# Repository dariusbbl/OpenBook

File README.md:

# OpenBook

# Block Diagram

# Hardware Components
#### Microcontroller – ESP32-C6
- **Core Architecture:** 32-bit RISC-V processor  
- **Wireless Support:** Integrated Wi-Fi 6 and Bluetooth Low Energy 5.0  
- **I/O Capabilities:** Supports multiple digital interfaces – SPI, I²C, UART, PWM, and general-purpose IO  
- **Power Features:** Low-energy design with deep sleep functionality for battery-powered applications

#### Real-Time Clock – DS3231SN
- **Accuracy:** ±2 ppm  
- **Communication:** I²C (`SDA`, `SCL`)  
- **Backup Power:** Supercapacitor-based retention

#### E-Paper Display
- **Connection Method:** 20-pin dedicated header  
- **Communication Protocol:** SPI + GPIO  
- **Key Signals:** `EPD_CS`, `EPD_DC`, `EPD_RST`, `EPD_BUSY`, etc.  
- **Advantages:** Zero power draw when idle, high readability in sunlight

#### MicroSD Card Slot
- **Interface:** SPI (connected to IO4 through IO9)  
- **Purpose:** Storing eBooks, setting and user configuration data  

#### Environmental Sensor – BME688
- **Measurements:** Temperature, Humidity, Pressure and VOCs  
- **Interface:** I²C  
- **Pins:** `SDA` – IO1, `SCL` – IO2  
- **Power Supply:** 3.3V  
- **Default Address:** `0x76` 

#### Environmental Sensor – BME688 Battery Fuel Gauge - MAX17048
- **Role:** Estimates remaining charge in LiPo(Lithium Polymer) battery
- **Protocol:** I²C (shared on IO1, IO2)  

#### Environmental Sensor – BME688 I²C Expansion – Qwiic / Stemma QT
- **Connector:** 4-pin (3V3, GND, SDA, SCL)  
- **Protocol:** I²C (`IO1`, `IO2`)  
- **Compatibility:** Plug-and-play with Adafruit / SparkFun modules  

#### Environmental Sensor – BME688 Voltage Supervisor – BD52xx
- **Purpose:** Monitors voltage levels, triggers safe reset  
- **Control Pin:** IO0

#### MCP73831 – Charging Controller
- **Function:** LiPo charging via USB (3.7V)  
- **Charging Current:** ~500 mA  
- **Indicator:** Status LED  

# BOM (Bill Of Materials)

| Componenta | Link | Datasheet |
|-----------|--------------|-----------|
| BUTTON | [Model](https://industry.panasonic.com/global/en/products/control/switch/light-touch/number/evqpuj02k) | [Datasheet](https://www.lcsc.com/datasheet/lcsc_datasheet_2201121800_PANASONIC-EVQPUJ02K_C2936858.pdf) |
| CAPACITOR | [Model](https://componentsearchengine.com/part-view/R0402%201%25%20100%20K%20(RC0402FR-07100KL)/YAGEO) | [Datasheet](//efaidnbmnnnibpcajpcglclefindmkaj/https://www.resistor.com/assets/pdf/0402tstd.pdf) |
| CPH3225A | [Model](https://www.snapeda.com/parts/CPH3225A/Seiko+Instruments/view-part/?ref=eda) | [Datasheet](https://octopart.com/datasheet/cph3225a-seiko-25340571) |
| EVQPUJ02K | [Model](https://industry.panasonic.com/global/en/products/control/switch/light-touch/number/evqpuj02k) | [Datasheet](https://www.lcsc.com/datasheet/lcsc_datasheet_2201121800_PANASONIC-EVQPUJ02K_C2936858.pdf) |
| KP-1608SURCK | [Model](https://www.snapeda.com/parts/KP-1608SURCK/Kingbright/view-part/?ref=search&t=LED%200603) | [Datasheet](//efaidnbmnnnibpcajpcglclefindmkaj/https://media.elv.com/file/107153_led_surck1608_data.pdf) |
| USBLC6-2SC6Y | [Model](https://www.snapeda.com/parts/USBLC6-2SC6Y/STMicroelectronics/view-part/?ref=eda) | [Datasheet](https://www.digikey.com/en/htmldatasheets/production/1375342/0/0/1/usblc6-2sc6y) |
| SD0805S020S1R0 | [Model](https://ro.mouser.com/ProductDetail/KYOCERA-AVX/SD0805S020S1R0?qs=jCA%252BPfw4LHbpkAoSnwrdjw%3D%3D) | [Datasheet](https://www.alldatasheet.com/view.jsp?Searchword=SD0805S&sField=2) |
| PGB1010603MR | [Model](https://www.snapeda.com/parts/PGB1010603MR/Littelfuse/view-part/?ref=eda) | [Datasheet](https://www.alldatasheet.com/view.jsp?Searchword=Pgb1010603mr&gad_source=1&gbraid=0AAAAADcdDU8aYfZtfJfdZ9I5j6RwZ_cbA&gclid=Cj0KCQjwqcO_BhDaARIsACz62vOPBOBe0eOh5gDUFkkKl4JBcbmoFZYtJ8BOnbaWqr_BuUCcVWvbutAaAmGkEALw_wcB) |
| BD5229G-TR  | [Model](https://componentsearchengine.com/part-view/BD5229G-TR/ROHM%20Semiconductor) | [Datasheet](https://www.lcsc.com/datasheet/lcsc_datasheet_2201131330_ROHM-Semicon-BD5229G-TR_C962636.pdf) |
| XC6220A331MR-G | [Model](https://componentsearchengine.com/part-view/XC6220A331MR-G/Torex) | [Datasheet](https://www.alldatasheet.com/view.jsp?Searchword=Xc6220&gad_source=1&gbraid=0AAAAADcdDU8aYfZtfJfdZ9I5j6RwZ_cbA&gclid=Cj0KCQjwqcO_BhDaARIsACz62vPS06NB6tLgniZzfaVpKNu1m811BNk6AEPfg4DbP6f5S8QWA_pW_UQaAv-0EALw_wcB) |
| XC6220A331MR-G | [Model](https://componentsearchengine.com/part-view/XC6220A331MR-G/Torex) | [Datasheet](https://www.alldatasheet.com/view.jsp?Searchword=Xc6220&gad_source=1&gbraid=0AAAAADcdDU8aYfZtfJfdZ9I5j6RwZ_cbA&gclid=Cj0KCQjwqcO_BhDaARIsACz62vMO5_aHsn35cIZBK6oCFuB_WOxz_zKu4yOHJ69-EnaUd5Jfas_Avm8aAuk5EALw_wcB) |
| USB4110-GF-A  | [Model](https://componentsearchengine.com/part-view/USB4110-GF-A/GCT%20(GLOBAL%20CONNECTOR%20TECHNOLOGY)) | [Datasheet](//efaidnbmnnnibpcajpcglclefindmkaj/https://gct.co/files/drawings/usb4110.pdf) |
| Adafruit | [Model](https://eu.mouser.com/ProductDetail/Adafruit/4208?qs=PzGy0jfpSMtbScLbr0L5dw%3D%3D) | [Datasheet](https://www.arrow.com/en/manufacturers/adafruit-industries/datasheets) |
| Bobina | [Model](https://store.comet.srl.ro/Catalogue/Product/43497/) | [Datasheet](https://www.scribd.com/document/814581278/Datasheet-Bobina) |
| PFMF | [Model](https://www.mouser.co.uk/ProductDetail/EPCOS-TDK/B72520T0350K062?qs=dEfas%2FXlABIszF52uu7vrg%3D%3D) | [Datasheet](https://ro.mouser.com/c/ds/circuit-protection/thermistors/resettable-fuses-pptc/?m=Schurter&series=PFMF) |
| DMG2305UX-7 | [Model](https://componentsearchengine.com/part-view/DMG2305UX-7/Diodes%20Incorporated) | [Datasheet](//efaidnbmnnnibpcajpcglclefindmkaj/https://www.mouser.com/datasheet/2/115/DMG2305UX-266242.pdf?srsltid=AfmBOop22k34YTJJra1xubiU6LPiN4M4JlcWbRoSNdxSGFak8uWgXPpK) |
| Si1308EDL-T1-GE3 | [Model](https://componentsearchengine.com/part-view/SI1308EDL-T1-GE3/Vishay) | [Datasheet](https://www.alldatasheet.com/view.jsp?Searchword=Si1308edl&gad_source=1&gbraid=0AAAAADcdDU-px713ONYSnQ2O-gcwqYcFq&gclid=Cj0KCQjwqcO_BhDaARIsACz62vN_Nz3MJOc6J_03gnVBm7aSqC8v9wyP0VD-iRKP-gFrYgdhLi99I14aAlVJEALw_wcB) |
| R0402 | [Model](https://componentsearchengine.com/part-view/R0402%201%25%20100%20K%20(RC0402FR-07100KL)/YAGEO) | [Datasheet](//efaidnbmnnnibpcajpcglclefindmkaj/https://www.resistor.com/assets/pdf/0402tstd.pdf) |
| BME680 | [Model](https://www.snapeda.com/parts/BME680/Bosch/view-part/?welcome=home) | [Datasheet](//efaidnbmnnnibpcajpcglclefindmkaj/https://www.bosch-sensortec.com/media/boschsensortec/downloads/datasheets/bst-bme680-ds001.pdf) |
| SMD Solder | [Model](https://grabcad.com/library/solder-jumpers-1) | [Datasheet]() |
| W25Q512JVEIQ | [Model](https://www.snapeda.com/parts/ESP32-C6-WROOM-1-N8/Espressif+Systems/view-part/?ref=eda) | [Datasheet](//efaidnbmnnnibpcajpcglclefindmkaj/https://www.mouser.com/datasheet/2/949/W25Q512JV_SPI_RevB_06252019_KMS-2487502.pdf?srsltid=AfmBOoquExqDVgxEELF9CzuOGxHos0CD1nQDROHD6Eebdm2foNzqozqU) |
| ESP32-C6-WROOM-1-N8 | [Model](https://www.snapeda.com/parts/ESP32-C6-WROOM-1-N8/Espressif+Systems/view-part/?ref=eda) | [Datasheet](//efaidnbmnnnibpcajpcglclefindmkaj/https://www.mouser.com/catalog/specsheets/Espressif_ESP32_C6_WROOM_1%20_Datasheet_V0.1_PRELIMINARY_en.pdf?srsltid=AfmBOooHQKNitqODRaaPjoZInfWKTacDER1t5uRK6sKqT13TrzvVo_B7) |
| DS3231SN# | [Model](https://www.snapeda.com/parts/DS3231SN%23/Analog+Devices/view-part/?ref=eda) | [Datasheet](https://www.alldatasheet.com/view.jsp?Searchword=Ds3231sn%20datasheet&gad_source=1&gbraid=0AAAAADcdDU-Gy9URfMxGmqiPg7ci5L3wR&gclid=Cj0KCQjwqcO_BhDaARIsACz62vMkK3ETSnW2w7mo0Fa-wgWJGn89AxWCyIND6k5X8MmoPl6hv6VWwT8aAiS-EALw_wcB) |
| MAX17048G+T10 | [Model](https://www.snapeda.com/parts/MAX17048G+T10/Analog+Devices/view-part/?ref=eda) | [Datasheet](https://www.alldatasheet.com/view.jsp?Searchword=Max17048&gad_source=1&gbraid=0AAAAADcdDU8aYfZtfJfdZ9I5j6RwZ_cbA&gclid=Cj0KCQjwqcO_BhDaARIsACz62vNa9xrVfzjCjADRwXD0RBbo4Nret3ywwteDGLJKZui8ZL8KdVlTE7caAvQxEALw_wcB) |
| MCP73831T-5ACI/OT | [Model](https://www.mouser.co.uk/ProductDetail/Microchip-Technology/MCP73831T-5ACI-OT?qs=hH%252BOa0VZEiAcgAcEkuamXg%3D%3D) | [Datasheet](//efaidnbmnnnibpcajpcglclefindmkaj/https://ww1.microchip.com/downloads/en/DeviceDoc/MCP73831-Family-Data-Sheet-DS20001984H.pdf) |

### ESP32-C6 Hardware Connections Overview  

| **Peripheral**               | **Connected Pin(s)**                                             | **Protocol** | **Functionality Description** |
|-----------------------------|------------------------------------------------------------------|--------------|-------------------------------|
| **E-Paper Display**         | IO7 (MOSI), IO6 (SCK), IO10 (CS), IO5 (DC), IO23 (RST), IO3 (BUSY) | SPI          | Sends visual data and manages display operations. |
| **MicroSD Card Module**     | IO7 (MOSI), IO6 (SCK), IO4 (SS_SD), IO2 (MISO)                   | SPI          | Enables saving and reading of e-book files. |
| **BME688 Environmental Sensor** | IO21 (SDA), IO22 (SCL)                                        | I2C          | Measures environmental factors like temperature, humidity, pressure, and gas levels. |
| **DS3231 RTC Module**       | IO21 (SDA), IO22 (SCL), IO18 (RST), IO1 (32KHz), IO0 (INT_RTC)   | I2C          | Maintains accurate timekeeping even when the main system is off. |
| **External NOR Flash**      | IO11 (CS), IO6 (SCK), IO2 (MISO), IO7 (MOSI)                     | SPI          | Offers extra non-volatile memory for storing application-specific data. |
| **Battery Status Monitor**  | IO21 (SDA), IO22 (SCL)                                           | I2C          | Monitors power level and battery condition. |
| **USB-C Interface**         | GPIOs via regulated voltage lines                                | USB          | Supplies power and facilitates programming access. |
| **User Input Buttons**      | IO9 (BOOT), IO15 (CHANGE), EN (RESET)                            | GPIO         | Detects user interaction through physical button presses. |

# Decision & Modifications
- To address the design checker errors, I adjusted the dimensions of several components.
- The main components were positioned exactly according to the provided specifications to ensure a perfect match between the PCB dimensions and the case. Component placement was carefully planned to allow for efficient routing. The battery was placed in the remaining free space within the case.
- A ground plane was created on both the top and bottom layers to improve signal integrity and reduce noise.
- Routing was performed on both the top and bottom layers. Power traces were placed exclusively on the top layer to avoid the use of vias.
- Diodes (SMD-Hole): The initial footprint included through-hole pads that were too narrow, potentially leading to soldering difficulties and poor connectivity. To address this, the pad dimensions were modified to 35 mil × 190 mil, improving both manufacturability and the reliability of the electrical contact.
- U4 – MAX17048G+T10: The VBAT power trace was routed with a width of 0.3 mm due to design constraints. However, the original footprint featured pin widths of just 0.27 mm, which caused mismatches and disrupted routing symmetry. The pad widths were therefore increased to match the trace width, ensuring consistent routing and improved layout balance.

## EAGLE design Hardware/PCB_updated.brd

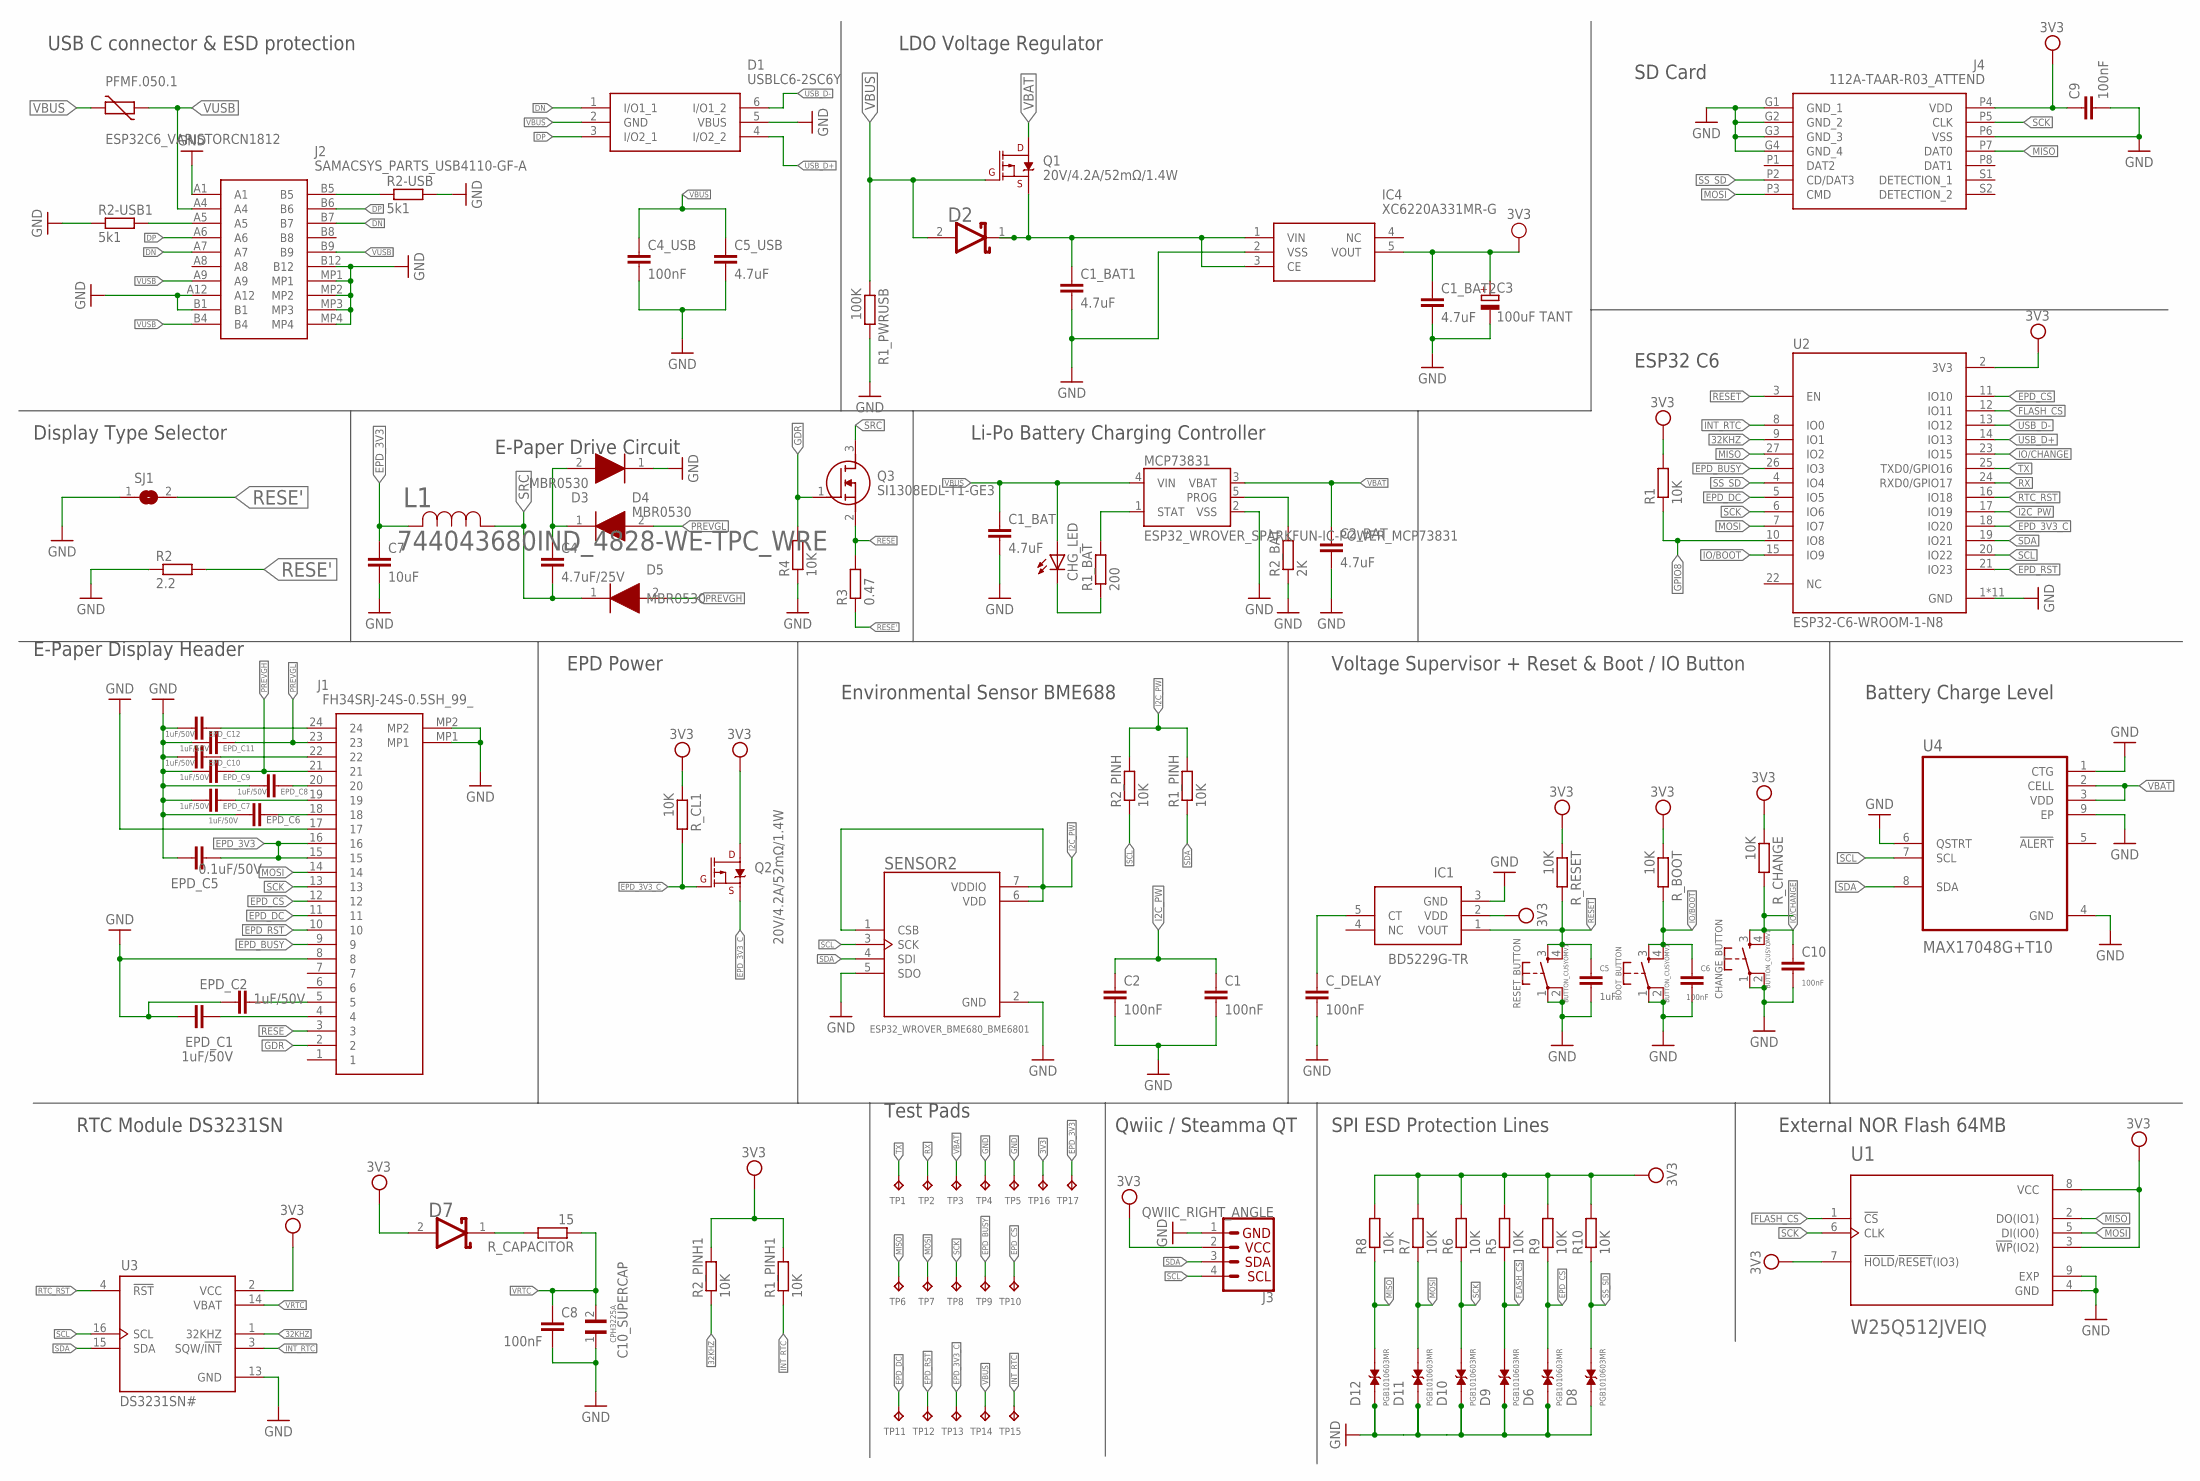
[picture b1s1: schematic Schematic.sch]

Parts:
BOOT_BUTTON: BUTTON_CUSYOMV1; MYBUTTON
C1, C2, C4_USB, C6, C8, C9, C10: 100nF; ESP32_WROVER_EAGLE-LTSPICE_C0402
C1_BAT, C1_BAT1, C1_BAT2, C2_BAT, C5_USB: 4.7uF; ESP32_WROVER_EAGLE-LTSPICE_C0402
C3: 100uF TANT; RCL_CT3528
C4: 4.7uF/25V; ESP32_WROVER_EAGLE-LTSPICE_C0402
C5: 1uF; ESP32_WROVER_EAGLE-LTSPICE_C0402
C7: 10uF; ESP32_WROVER_EAGLE-LTSPICE_C0402
C10_SUPERCAP: CPH3225A; CAPCP3225X100N
CHANGE_BUTTON: BUTTON_CUSYOMV1; MYBUTTON
CHG_LED: ADAFRUIT_LEDCHIP-LED0603; ADAFRUIT_CHIP-LED0603
C_DELAY: 100nF; ESP32_WROVER_EAGLE-LTSPICE_C0402
D1: USBLC6-2SC6Y; SOT95P280X145-6N
D2, D7: ESP32_WROVER_AVX---SD0805S020S1R0_AVX_SD0805S020S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; ESP32_WROVER_AVX---SD0805S020S1R0_AVX_SD0805S020S1R0_0
D3, D4, D5: MBR0530; SOD3716X135N
D6, D8, D9, D10, D11, D12: PGB1010603MR; DIOC1608X36N
EPD_C1, EPD_C2, EPD_C6, EPD_C7, EPD_C8, EPD_C9, EPD_C10, EPD_C11, EPD_C12: 1uF/50V; ESP32_WROVER_EAGLE-LTSPICE_C0402
EPD_C5: 0.1uF/50V; ESP32_WROVER_EAGLE-LTSPICE_C0402
IC1: BD5229G-TR; SOT95P280X125-5N
IC4: XC6220A331MR-G; SOT95P280X120-5N
J1: FH34SRJ-24S-0.5SH_99_; FH34SRJ24S05SH99
J2: SAMACSYS_PARTS_USB4110-GF-A; SAMACSYS_PARTS_USB4110GFA
J3: QWIIC_RIGHT_ANGLE; JST04_1MM_RA
J4: 112A-TAAR-R03_ATTEND; 112ATAARR03ATTEND
L1: 744043680IND_4828-WE-TPC_WRE; IND_4828-WE-TPC_WRE
MCP73831: ESP32_WROVER_SPARKFUN-IC-POWER_MCP73831; ESP32_WROVER_SPARKFUN-IC-POWER_SOT23-5
PFMF.050.1: ESP32C6_VARISTORCN1812; ESP32C6_VARISTOR_CT/CN1812
Q1, Q2: 20V/4.2A/52mΩ/1.4W; ESP32_WROVER_SPARKFUN-DISCRETESEMI_SOT23-3
Q3: SI1308EDL-T1-GE3; SOT65P210X110-3N
R1, R1_PINH, R1_PINH1, R2_PINH, R2_PINH1, R4, R5, R6, R7, R9, R10: 10K; ESP32_WROVER_EAGLE-LTSPICE_R0402
R1_BAT: 200; ESP32_WROVER_EAGLE-LTSPICE_R0402
R1_PWRUSB: 100K; ESP32_WROVER_EAGLE-LTSPICE_R0402
R2: 2.2; ESP32_WROVER_EAGLE-LTSPICE_R0402
R2-USB, R2-USB1: 5k1; ESP32_WROVER_EAGLE-LTSPICE_R0402
R2_BAT: 2K; ESP32_WROVER_EAGLE-LTSPICE_R0402
R3: 0.47; ESP32_WROVER_EAGLE-LTSPICE_R0402
R8: 10k; ESP32_WROVER_EAGLE-LTSPICE_R0402
RESET_BUTTON: BUTTON_CUSYOMV1; MYBUTTON
R_BOOT: 10K; ESP32_WROVER_EAGLE-LTSPICE_R0402
R_CAPACITOR: 15; ESP32_WROVER_EAGLE-LTSPICE_R0402
R_CHANGE: 10K; ESP32_WROVER_EAGLE-LTSPICE_R0402
R_CL1: 10K; ESP32_WROVER_EAGLE-LTSPICE_R0402
R_RESET: 10K; ESP32_WROVER_EAGLE-LTSPICE_R0402
SENSOR2: ESP32_WROVER_BME680_BME6801; ESP32_WROVER_BME680_PSON80P300X300X100-8N
SJ1: SJ
TP1, TP2, TP3, TP4, TP5, TP6, TP7, TP8, TP9, TP10, TP11, TP12, TP13, TP14, TP15, TP16, TP17: TPTP20R; TP20R
U1: W25Q512JVEIQ; SON127P600X800X80-9N
U2: ESP32-C6-WROOM-1-N8; XCVR_ESP32-C6-WROOM-1-N8
U3: DS3231SN#; SOIC127P1032X265-16N
U4: MAX17048G+T10; SON50P200X200X80-9N

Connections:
3V3: C1_BAT2.1, C3.+, C9.1, D7.2 (ANODE), IC1.2 (VDD), IC4.5 (VOUT), J3.2, J4.P4 (VDD), Q2.3 (D), R1.2, R1_PINH1.2, R2_PINH1.2, R5.2, R6.2, R7.2, R8.2, R9.2, R10.2, R_BOOT.1, R_CHANGE.1, R_CL1.1, R_RESET.1, TP16.TP, U1.3 (!WP!(IO2)), U1.7 (!HOLD!/!RESET!(IO3)), U1.8 (VCC), U2.2 (3V3), U3.2 (VCC)
32KHZ: R2_PINH1.1, U2.9 (IO1), U3.1 (32KHZ)
DN: D1.1 (I/O1_1), J2.A7, J2.B7
DP: D1.3 (I/O2_1), J2.A6, J2.B6
EPD_3V3: C7.1, EPD_C5.2, J1.15, J1.16, L1.2, TP17.TP
EPD_3V3_C: Q2.1 (G), Q2.2 (S), R_CL1.2, TP13.TP, U2.18 (IO20)
EPD_BUSY: J1.9, TP9.TP, U2.26 (IO3)
EPD_CS: D6.2, J1.12, R9.1, TP10.TP, U2.11 (IO10)
EPD_DC: J1.11, TP11.TP, U2.5 (IO5)
EPD_RST: J1.10, TP12.TP, U2.21 (IO23)
FLASH_CS: D9.2, R5.1, U1.1 (!CS), U2.12 (IO11)
GDR: J1.2, Q3.1 (G), R4.2
GND: BOOT_BUTTON.1, BOOT_BUTTON.2, C1.2, C1_BAT.2, C1_BAT1.2, C1_BAT2.2, C2.2, C2_BAT.2, C3.-, C4_USB.2, C5.2, C5_USB.2, C6.2, C7.2, C8.2, C9.2, C10.2, C10_SUPERCAP.1, CHANGE_BUTTON.1, CHANGE_BUTTON.2, C_DELAY.2, D1.5 (VBUS), D3.1 (K), D6.1, D8.1, D9.1, D10.1, D11.1, D12.1, EPD_C1.1, EPD_C2.1, EPD_C5.1, EPD_C6.2, EPD_C7.2, EPD_C8.2, EPD_C9.2, EPD_C10.2, EPD_C11.2, EPD_C12.2, IC1.3 (GND), IC4.2 (VSS), J1.8, J1.17, J1.MP1, J1.MP2, J2.A1, J2.A12, J2.B1, J2.B12, J2.MP1, J2.MP2, J2.MP3, J2.MP4, J3.1, J4.G1 (GND_1), J4.G2 (GND_2), J4.G3 (GND_3), J4.G4 (GND_4), J4.P6 (VSS), MCP73831.2 (VSS), R1_PWRUSB.2, R2.1, R2-USB.2, R2-USB1.1, R2_BAT.1, R4.1, RESET_BUTTON.1, RESET_BUTTON.2, SENSOR2.2 (GND), SENSOR2.5 (SDO), SJ1.1, TP4.TP, TP5.TP, U1.4 (GND), U1.9 (EXP), U2.1 (GND), U2.28 (GND), U2.29_1 (GND), U2.29_2 (GND), U2.29_3 (GND), U2.29_4 (GND), U2.29_5 (GND), U2.29_6 (GND), U2.29_7 (GND), U2.29_8 (GND), U2.29_9 (GND), U3.13 (GND), U4.1 (CTG), U4.4 (GND), U4.6 (QSTRT), U4.9 (EP)
GPIO8: R1.1, U2.10 (IO8)
I2C_PW: C1.1, C2.1, R1_PINH.2, R2_PINH.2, SENSOR2.1 (CSB), SENSOR2.6 (VDD), SENSOR2.7 (VDDIO), U2.17 (IO19)
INT_RTC: R1_PINH1.1, TP15.TP, U2.8 (IO0), U3.3 (SQW/!INT)
IO/BOOT: BOOT_BUTTON.3, BOOT_BUTTON.4, C6.1, R_BOOT.2, U2.15 (IO9)
IO/CHANGE: C10.1, CHANGE_BUTTON.3, CHANGE_BUTTON.4, R_CHANGE.2, U2.23 (IO15)
MISO: D12.2, J4.P7 (DAT0), R8.1, TP6.TP, U1.2 (DO(IO1)), U2.27 (IO2)
MOSI: D11.2, J1.14, J4.P3 (CMD), R7.1, TP7.TP, U1.5 (DI(IO0)), U2.7 (IO7)
unnamed: J2.A5, R2-USB1.2
unnamed: J2.B5, R2-USB.1
unnamed: C1_BAT1.1, D2.1 (CATHODE), IC4.1 (VIN), IC4.3 (CE), Q1.2 (S)
unnamed: C4.1, D3.2 (A), D4.1 (K)
unnamed: MCP73831.5 (PROG), R2_BAT.2
unnamed: MCP73831.1 (STAT), R1_BAT.2
unnamed: CHG_LED.C, R1_BAT.1
unnamed: EPD_C6.1, J1.18
unnamed: D7.1 (CATHODE), R_CAPACITOR.2
unnamed: EPD_C1.2, J1.4
unnamed: EPD_C2.2, J1.5
unnamed: EPD_C7.1, J1.19
unnamed: EPD_C8.1, J1.20
unnamed: EPD_C10.1, J1.22
unnamed: EPD_C12.1, J1.24
unnamed: C_DELAY.1, IC1.5 (CT)
PREVGH: D5.2 (A), EPD_C9.1, J1.21
PREVGL: D4.2 (A), EPD_C11.1, J1.23
RESE: J1.3, Q3.2 (S), R3.2
RESE': R2.2, R3.1, SJ1.2
RESET: C5.1, IC1.1 (VOUT), RESET_BUTTON.3, RESET_BUTTON.4, R_RESET.2, U2.3 (EN)
RTC_RST: U2.16 (IO18), U3.4 (!RST)
RX: TP2.TP, U2.24 (RXD0/GPIO17)
SCK: D10.2, J1.13, J4.P5 (CLK), R6.1, TP8.TP, U1.6 (CLK), U2.6 (IO6)
SCL: J3.4, R2_PINH.1, SENSOR2.3 (SCK), U2.20 (IO22), U3.16 (SCL), U4.7 (SCL)
SDA: J3.3, R1_PINH.1, SENSOR2.4 (SDI), U2.19 (IO21), U3.15 (SDA), U4.8 (SDA)
SRC: C4.2, D5.1 (K), L1.1, Q3.3 (D)
SS_SD: D8.2, J4.P2 (CD/DAT3), R10.1, U2.4 (IO4)
TX: TP1.TP, U2.25 (TXD0/GPIO16)
USB_D+: D1.4 (I/O2_2), U2.14 (IO13)
USB_D-: D1.6 (I/O1_2), U2.13 (IO12)
VBAT: C2_BAT.1, MCP73831.3 (VBAT), Q1.3 (D), TP3.TP, U4.2 (CELL), U4.3 (VDD)
VBUS: C1_BAT.1, C4_USB.1, C5_USB.1, CHG_LED.A, D1.2 (GND), D2.2 (ANODE), MCP73831.4 (VIN), PFMF.050.1.2, Q1.1 (G), R1_PWRUSB.1, TP14.TP
VRTC: C8.1, C10_SUPERCAP.2, R_CAPACITOR.1, U3.14 (VBAT)
VUSB: J2.A4, J2.A9, J2.B4, J2.B9, PFMF.050.1.1

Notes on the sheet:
USB C connector & ESD protection
Display Type Selector
SD Card
LDO Voltage Regulator
E-Paper Drive Circuit
Li-Po Battery Charging Controller
ESP32 C6
Battery Charge Level
External NOR Flash 64MB
E-Paper Display Header
EPD Power
Environmental Sensor BME688
Voltage Supervisor + Reset & Boot / IO Button
RTC Module DS3231SN
Test Pads
Qwiic / Steamma QT
SPI ESD Protection Lines

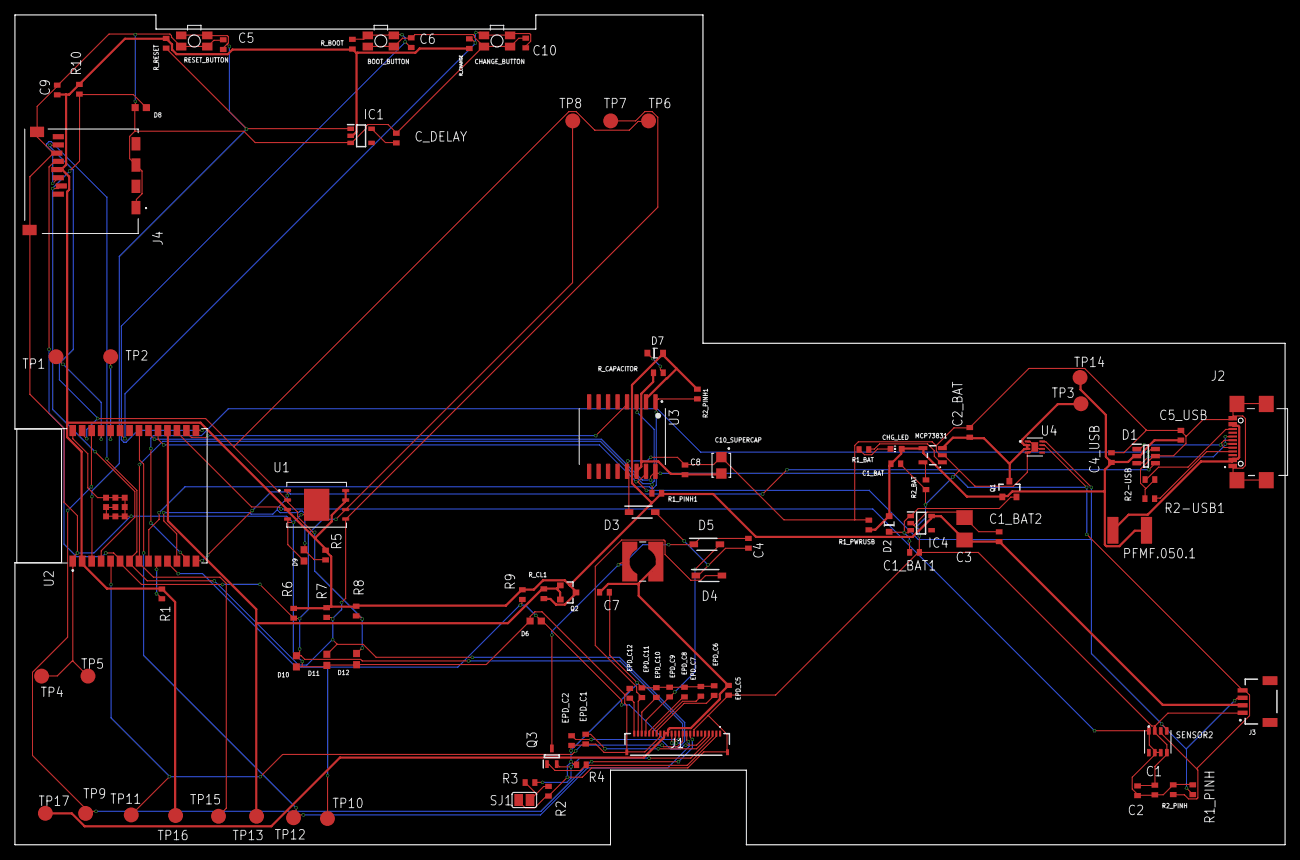
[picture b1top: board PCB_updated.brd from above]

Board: 2 copper layers, 170.2 x 111.2 mm, 103 parts (0 on the bottom side), 55 nets.

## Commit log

2025-04-05 Create LICENSE
2025-04-05 Add files

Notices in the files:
parts and their libraries:
COPYRIGHT: Copyright (C) 2024 Ultra Librarian. All rights reserved.
